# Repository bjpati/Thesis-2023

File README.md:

# Thesis-2023
The goal of this thesis is to develop an embedded test system for monitoring current in a multiple channel neuromuscular electrical stimulation (NMES) system. The system is designed to detect overcurrent and leakage conditions and protect the patient from injury.

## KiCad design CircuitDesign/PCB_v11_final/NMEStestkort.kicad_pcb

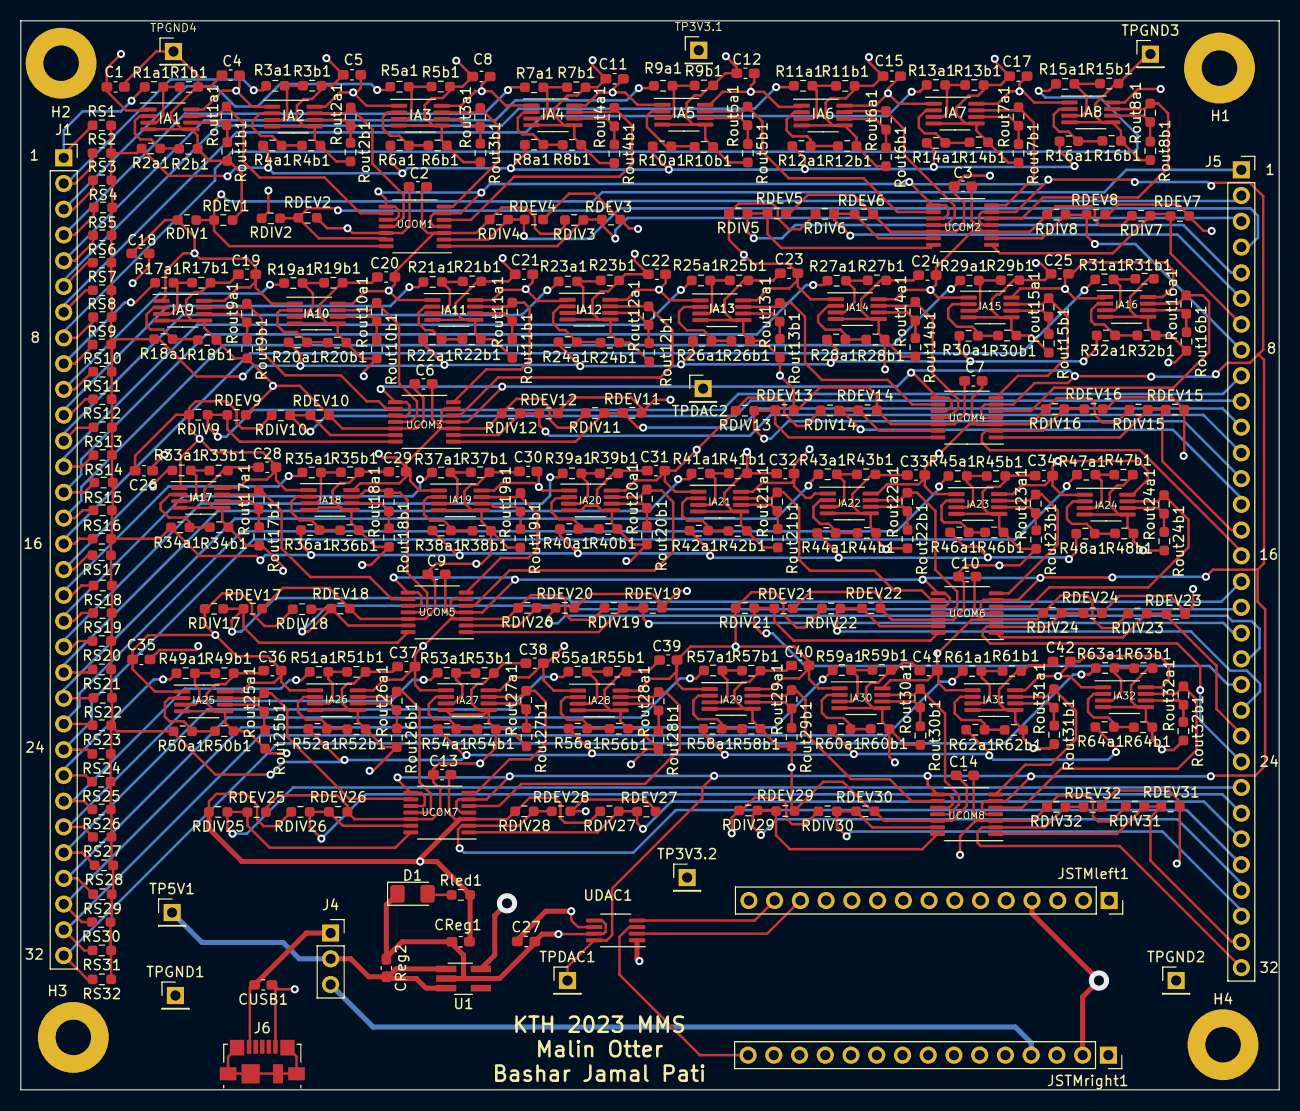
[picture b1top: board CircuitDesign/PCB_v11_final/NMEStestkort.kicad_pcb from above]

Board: 4 copper layers, 124.2 x 105.5 mm, 395 parts (0 on the bottom side), 203 nets.

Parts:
C1, C2, C3, C4, C5, C6, C7, C8, C9, C10, C11, C12, C13, C14, C15, C17, C18, C19, C20, C21, C22, C23, C24, C25, C26, C27, C28, C29, C30, C31, C32, C33, C34, C35, C36, C37, C38, C39, C40, C41, C42: 0.1u; C_0603_1608Metric_Pad1.08x0.95mm_HandSolder
CReg1, CReg2: 1u; C_0603_1608Metric_Pad1.08x0.95mm_HandSolder
CUSB1: 1u; C_0603_1608Metric_Pad1.08x0.95mm_HandSolder
D1: LED; LED_1206_3216Metric_Pad1.42x1.75mm_HandSolder
H1, H2, H3, H4: MountingHole; MountingHole_3.5mm_Pad
IA1, IA2, IA3, IA4, IA5, IA6, IA7, IA8, IA9, IA10, IA11, IA12, IA13, IA14, IA15, IA16, IA17, IA18, IA19, IA20, IA21, IA22, IA23, IA24, IA25, IA26, IA27, IA28, IA29, IA30, IA31, IA32: MCP6N16; MSOP-8_3x3mm_P0.65mm
J1, J5: Conn_01x32_Female; PinSocket_1x32_P2.54mm_Vertical
J4: Conn_01x03_Female; PinSocket_1x03_P2.54mm_Vertical
J6: USB_B_Micro; USB_Micro-B_Molex_47346-0001
JSTMleft1: Conn_01x15_Female; PinSocket_1x15_P2.54mm_Vertical
JSTMright1: Conn_01x15_Female; PinSocket_1x15_P2.54mm_Vertical
R1a1, R2a1, R3a1, R4a1, R5a1, R6a1, R7a1, R8a1, R9a1, R10a1, R11a1, R12a1, R13a1, R14a1, R15a1, R16a1, R17a1, R18a1, R19a1, R20a1, R21a1, R22a1, R23a1, R24a1, R25a1, R26a1, R27a1, R28a1, R29a1, R30a1, R31a1, R32a1, R33a1, R34a1, R35a1, R36a1, R37a1, R38a1, R39a1, R40a1, R41a1, R42a1, R43a1, R44a1, R45a1, R46a1, R47a1, R48a1, R49a1, R50a1, R51a1, R52a1, R53a1, R54a1, R55a1, R56a1, R57a1, R58a1, R59a1, R60a1, R61a1, R62a1, R63a1, R64a1: 47k; R_0603_1608Metric_Pad0.98x0.95mm_HandSolder
R1b1, R2b1, R3b1, R4b1, R5b1, R6b1, R7b1, R8b1, R9b1, R10b1, R11b1, R12b1, R13b1, R14b1, R15b1, R16b1, R17b1, R18b1, R19b1, R20b1, R21b1, R22b1, R23b1, R24b1, R25b1, R26b1, R27b1, R28b1, R29b1, R30b1, R31b1, R32b1, R33b1, R34b1, R35b1, R36b1, R37b1, R38b1, R39b1, R40b1, R41b1, R42b1, R43b1, R44b1, R45b1, R46b1, R47b1, R48b1, R49b1, R50b1, R51b1, R52b1, R53b1, R54b1, R55b1, R56b1, R57b1, R58b1, R59b1, R60b1, R61b1, R62b1, R63b1, R64b1: 470; R_0603_1608Metric_Pad0.98x0.95mm_HandSolder
RDEV1, RDEV2, RDEV3, RDEV4, RDEV5, RDEV6, RDEV7, RDEV8, RDEV9, RDEV10, RDEV11, RDEV12, RDEV13, RDEV14, RDEV15, RDEV16, RDEV17, RDEV18, RDEV19, RDEV20, RDEV21, RDEV22, RDEV23, RDEV24, RDEV25, RDEV26, RDEV27, RDEV28, RDEV29, RDEV30, RDEV31, RDEV32: 6k2; R_0603_1608Metric_Pad0.98x0.95mm_HandSolder
RDIV1, RDIV2, RDIV3, RDIV4, RDIV5, RDIV6, RDIV7, RDIV8, RDIV9, RDIV10, RDIV11, RDIV12, RDIV13, RDIV14, RDIV15, RDIV16, RDIV17, RDIV18, RDIV19, RDIV20, RDIV21, RDIV22, RDIV23, RDIV24, RDIV25, RDIV26, RDIV27, RDIV28, RDIV29, RDIV30, RDIV31, RDIV32: 2k2; R_0603_1608Metric_Pad0.98x0.95mm_HandSolder
RS1, RS2, RS3, RS4, RS5, RS6, RS7, RS8, RS9, RS10, RS11, RS12, RS13, RS14, RS15, RS16, RS17, RS18, RS19, RS20, RS21, RS22, RS23, RS24, RS25, RS26, RS27, RS28, RS29, RS30, RS31, RS32: 500; R_0603_1608Metric_Pad0.98x0.95mm_HandSolder
Rled1: 1k; R_0603_1608Metric_Pad0.98x0.95mm_HandSolder
Rout1a1, Rout2a1, Rout3a1, Rout4a1, Rout5a1, Rout6a1, Rout7a1, Rout8a1, Rout9a1, Rout10a1, Rout11a1, Rout12a1, Rout13a1, Rout14a1, Rout15a1, Rout16a1, Rout17a1, Rout18a1, Rout19a1, Rout20a1, Rout21a1, Rout22a1, Rout23a1, Rout24a1, Rout25a1, Rout26a1, Rout27a1, Rout28a1, Rout29a1, Rout30a1, Rout31a1, Rout32a1: 12k; R_0603_1608Metric_Pad0.98x0.95mm_HandSolder
Rout1b1, Rout2b1, Rout3b1, Rout4b1, Rout5b1, Rout6b1, Rout7b1, Rout8b1, Rout9b1, Rout10b1, Rout11b1, Rout12b1, Rout13b1, Rout14b1, Rout15b1, Rout16b1, Rout17b1, Rout18b1, Rout19b1, Rout20b1, Rout21b1, Rout22b1, Rout23b1, Rout24b1, Rout25b1, Rout26b1, Rout27b1, Rout28b1, Rout29b1, Rout30b1, Rout31b1, Rout32b1: 1k; R_0603_1608Metric_Pad0.98x0.95mm_HandSolder
TP3V3.1, TP3V3.2: Conn_01x02_Female; PinHeader_1x01_P2.54mm_Vertical
TP5V1: Conn_01x01_Female; PinHeader_1x01_P2.54mm_Vertical
TPDAC1, TPDAC2: Conn_01x01_Female; PinHeader_1x01_P2.54mm_Vertical
TPGND1, TPGND2, TPGND3, TPGND4: Conn_01x02_Female; PinHeader_1x01_P2.54mm_Vertical
U1: ADP151; TSOT-23-5_HandSoldering
UCOM1, UCOM2, UCOM3, UCOM4, UCOM5, UCOM6, UCOM7, UCOM8: LM339; TSSOP-14_4.4x5mm_P0.65mm
UDAC1: MCP4921; MSOP-8_3x3mm_P0.65mm

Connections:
+3.3V: C1.1, C2.1, C3.1, C4.1, C5.1, C6.1, C7.1, C8.1, C9.1, C10.1, C11.1, C12.1, C13.1, C14.1, C15.1, C17.1, C18.1, C19.1, C20.1, C21.1, C22.1, C23.1, C24.1, C25.1, C26.1, C27.1, C28.1, C29.1, C30.1, C31.1, C32.1, C33.1, C34.1, C35.1, C36.1, C37.1, C38.1, C39.1, C40.1, C41.1, C42.1, CReg1.1, IA1.1 (EN), IA1.8 (V+), IA2.1 (EN), IA2.8 (V+), IA3.1 (EN), IA3.8 (V+), IA4.1 (EN), IA4.8 (V+), IA5.1 (EN), IA5.8 (V+), IA6.1 (EN), IA6.8 (V+), IA7.1 (EN), IA7.8 (V+), IA8.1 (EN), IA8.8 (V+), IA9.1 (EN), IA9.8 (V+), IA10.1 (EN), IA10.8 (V+), IA11.1 (EN), IA11.8 (V+), IA12.1 (EN), IA12.8 (V+), IA13.1 (EN), IA13.8 (V+), IA14.1 (EN), IA14.8 (V+), IA15.1 (EN), IA15.8 (V+), IA16.1 (EN), IA16.8 (V+), IA17.1 (EN), IA17.8 (V+), IA18.1 (EN), IA18.8 (V+), IA19.1 (EN), IA19.8 (V+), IA20.1 (EN), IA20.8 (V+), IA21.1 (EN), IA21.8 (V+), IA22.1 (EN), IA22.8 (V+), IA23.1 (EN), IA23.8 (V+), IA24.1 (EN), IA24.8 (V+), IA25.1 (EN), IA25.8 (V+), IA26.1 (EN), IA26.8 (V+), IA27.1 (EN), IA27.8 (V+), IA28.1 (EN), IA28.8 (V+), IA29.1 (EN), IA29.8 (V+), IA30.1 (EN), IA30.8 (V+), IA31.1 (EN), IA31.8 (V+), IA32.1 (EN), IA32.8 (V+), RDIV1.2, RDIV2.2, RDIV3.2, RDIV4.2, RDIV5.2, RDIV6.2, RDIV7.2, RDIV8.2, RDIV9.2, RDIV10.2, RDIV11.2, RDIV12.2, RDIV13.2, RDIV14.2, RDIV15.2, RDIV16.2, RDIV17.2, RDIV18.2, RDIV19.2, RDIV20.2, RDIV21.2, RDIV22.2, RDIV23.2, RDIV24.2, RDIV25.2, RDIV26.2, RDIV27.2, RDIV28.2, RDIV29.2, RDIV30.2, RDIV31.2, RDIV32.2, Rled1.2, TP3V3.1.1, TP3V3.2.1, U1.5 (VOUT), UCOM1.3 (V+), UCOM2.3 (V+), UCOM3.3 (V+), UCOM4.3 (V+), UCOM5.3 (V+), UCOM6.3 (V+), UCOM7.3 (V+), UCOM8.3 (V+), UDAC1.1 (Vdd), UDAC1.6 (Vref)
+5V: CReg2.2, J4.2, TP5V1.1, U1.1 (VIN), U1.3 (EN)
+5V MCU: J4.3, JSTMright1.4
+5V USB: CUSB1.2, J4.1, J6.1 (VBUS)
DAC output: TPDAC1.1, TPDAC2.1, UCOM1.4 (-), UCOM1.6 (-), UCOM1.8 (-), UCOM1.10 (-), UCOM2.4 (-), UCOM2.6 (-), UCOM2.8 (-), UCOM2.10 (-), UCOM3.4 (-), UCOM3.6 (-), UCOM3.8 (-), UCOM3.10 (-), UCOM4.4 (-), UCOM4.6 (-), UCOM4.8 (-), UCOM4.10 (-), UCOM5.4 (-), UCOM5.6 (-), UCOM5.8 (-), UCOM5.10 (-), UCOM6.4 (-), UCOM6.6 (-), UCOM6.8 (-), UCOM6.10 (-), UCOM7.4 (-), UCOM7.6 (-), UCOM7.8 (-), UCOM7.10 (-), UCOM8.4 (-), UCOM8.6 (-), UCOM8.8 (-), UCOM8.10 (-), UDAC1.8 (Vout)
GND: C1.2, C2.2, C3.2, C4.2, C5.2, C6.2, C7.2, C8.2, C9.2, C10.2, C11.2, C12.2, C13.2, C14.2, C15.2, C17.2, C18.2, C19.2, C20.2, C21.2, C22.2, C23.2, C24.2, C25.2, C26.2, C27.2, C28.2, C29.2, C30.2, C31.2, C32.2, C33.2, C34.2, C35.2, C36.2, C37.2, C38.2, C39.2, C40.2, C41.2, C42.2, CReg1.2, CReg2.1, CUSB1.1, D1.1 (K), IA1.4 (V-), IA1.5 (Vref), IA2.4 (V-), IA2.5 (Vref), IA3.4 (V-), IA3.5 (Vref), IA4.4 (V-), IA4.5 (Vref), IA5.4 (V-), IA5.5 (Vref), IA6.4 (V-), IA6.5 (Vref), IA7.4 (V-), IA7.5 (Vref), IA8.4 (V-), IA8.5 (Vref), IA9.4 (V-), IA9.5 (Vref), IA10.4 (V-), IA10.5 (Vref), IA11.4 (V-), IA11.5 (Vref), IA12.4 (V-), IA12.5 (Vref), IA13.4 (V-), IA13.5 (Vref), IA14.4 (V-), IA14.5 (Vref), IA15.4 (V-), IA15.5 (Vref), IA16.4 (V-), IA16.5 (Vref), IA17.4 (V-), IA17.5 (Vref), IA18.4 (V-), IA18.5 (Vref), IA19.4 (V-), IA19.5 (Vref), IA20.4 (V-), IA20.5 (Vref), IA21.4 (V-), IA21.5 (Vref), IA22.4 (V-), IA22.5 (Vref), IA23.4 (V-), IA23.5 (Vref), IA24.4 (V-), IA24.5 (Vref), IA25.4 (V-), IA25.5 (Vref), IA26.4 (V-), IA26.5 (Vref), IA27.4 (V-), IA27.5 (Vref), IA28.4 (V-), IA28.5 (Vref), IA29.4 (V-), IA29.5 (Vref), IA30.4 (V-), IA30.5 (Vref), IA31.4 (V-), IA31.5 (Vref), IA32.4 (V-), IA32.5 (Vref), J6.5 (GND), JSTMleft1.4, JSTMright1.2, R1b1.2, R2b1.2, R3b1.2, R4b1.2, R5b1.2, R6b1.2, R7b1.2, R8b1.2, R9b1.2, R10b1.2, R11b1.2, R12b1.2, R13b1.2, R14b1.2, R15b1.2, R16b1.2, R17b1.2, R18b1.2, R19b1.2, R20b1.2, R21b1.2, R22b1.2, R23b1.2, R24b1.2, R25b1.2, R26b1.2, R27b1.2, R28b1.2, R29b1.2, R30b1.2, R31b1.2, R32b1.2, R33b1.2, R34b1.2, R35b1.2, R36b1.2, R37b1.2, R38b1.2, R39b1.2, R40b1.2, R41b1.2, R42b1.2, R43b1.2, R44b1.2, R45b1.2, R46b1.2, R47b1.2, R48b1.2, R49b1.2, R50b1.2, R51b1.2, R52b1.2, R53b1.2, R54b1.2, R55b1.2, R56b1.2, R57b1.2, R58b1.2, R59b1.2, R60b1.2, R61b1.2, R62b1.2, R63b1.2, R64b1.2, RDEV1.1, RDEV2.1, RDEV3.1, RDEV4.1, RDEV5.1, RDEV6.1, RDEV7.1, RDEV8.1, RDEV9.1, RDEV10.1, RDEV11.1, RDEV12.1, RDEV13.1, RDEV14.1, RDEV15.1, RDEV16.1, RDEV17.1, RDEV18.1, RDEV19.1, RDEV20.1, RDEV21.1, RDEV22.1, RDEV23.1, RDEV24.1, RDEV25.1, RDEV26.1, RDEV27.1, RDEV28.1, RDEV29.1, RDEV30.1, RDEV31.1, RDEV32.1, Rout1b1.2, Rout2b1.2, Rout3b1.2, Rout4b1.2, Rout5b1.2, Rout6b1.2, Rout7b1.2, Rout8b1.2, Rout9b1.2, Rout10b1.2, Rout11b1.2, Rout12b1.2, Rout13b1.2, Rout14b1.2, Rout15b1.2, Rout16b1.2, Rout17b1.2, Rout18b1.2, Rout19b1.2, Rout20b1.2, Rout21b1.2, Rout22b1.2, Rout23b1.2, Rout24b1.2, Rout25b1.2, Rout26b1.2, Rout27b1.2, Rout28b1.2, Rout29b1.2, Rout30b1.2, Rout31b1.2, Rout32b1.2, TPGND1.1, TPGND2.1, TPGND3.1, TPGND4.1, U1.2 (GND), UCOM1.12 (V-), UCOM2.12 (V-), UCOM3.12 (V-), UCOM4.12 (V-), UCOM5.12 (V-), UCOM6.12 (V-), UCOM7.12 (V-), UCOM8.12 (V-), UDAC1.5 (~LDAC), UDAC1.7 (Vss)
unnamed: D1.2 (A), Rled1.1
unnamed: IA1.2 (-), R2a1.1, R2b1.1
unnamed: IA1.3 (+), R1a1.1, R1b1.1
unnamed: IA1.6 (Vfg), Rout1a1.1, Rout1b1.1
unnamed: IA1.7 (Vout), Rout1a1.2, UCOM1.9 (+)
unnamed: IA2.2 (-), R4a1.1, R4b1.1
unnamed: IA2.3 (+), R3a1.1, R3b1.1
unnamed: IA2.6 (Vfg), Rout2a1.1, Rout2b1.1
unnamed: IA2.7 (Vout), Rout2a1.2, UCOM1.11 (+)
unnamed: IA3.2 (-), R6a1.1, R6b1.1
unnamed: IA3.3 (+), R5a1.1, R5b1.1
unnamed: IA3.6 (Vfg), Rout3a1.1, Rout3b1.1
unnamed: IA3.7 (Vout), Rout3a1.2, UCOM1.7 (+)
unnamed: IA4.2 (-), R8a1.1, R8b1.1
unnamed: IA4.3 (+), R7a1.1, R7b1.1
unnamed: IA4.6 (Vfg), Rout4a1.1, Rout4b1.1
unnamed: IA4.7 (Vout), Rout4a1.2, UCOM1.5 (+)
unnamed: IA5.2 (-), R10a1.1, R10b1.1
unnamed: IA5.3 (+), R9a1.1, R9b1.1
unnamed: IA5.6 (Vfg), Rout5a1.1, Rout5b1.1
unnamed: IA5.7 (Vout), Rout5a1.2, UCOM2.9 (+)
unnamed: IA6.2 (-), R12a1.1, R12b1.1
unnamed: IA6.3 (+), R11a1.1, R11b1.1
unnamed: IA6.6 (Vfg), Rout6a1.1, Rout6b1.1
unnamed: IA6.7 (Vout), Rout6a1.2, UCOM2.11 (+)
unnamed: IA7.2 (-), R14a1.1, R14b1.1
unnamed: IA7.3 (+), R13a1.1, R13b1.1
unnamed: IA7.6 (Vfg), Rout7a1.1, Rout7b1.1
unnamed: IA7.7 (Vout), Rout7a1.2, UCOM2.7 (+)
unnamed: IA8.2 (-), R16a1.1, R16b1.1
unnamed: IA8.3 (+), R15a1.1, R15b1.1
unnamed: IA8.6 (Vfg), Rout8a1.1, Rout8b1.1
unnamed: IA8.7 (Vout), Rout8a1.2, UCOM2.5 (+)
unnamed: IA9.2 (-), R18a1.1, R18b1.1
unnamed: IA9.3 (+), R17a1.1, R17b1.1
unnamed: IA9.6 (Vfg), Rout9a1.1, Rout9b1.1
unnamed: IA9.7 (Vout), Rout9a1.2, UCOM3.9 (+)
unnamed: IA10.2 (-), R20a1.1, R20b1.1
unnamed: IA10.3 (+), R19a1.1, R19b1.1
unnamed: IA10.6 (Vfg), Rout10a1.1, Rout10b1.1
unnamed: IA10.7 (Vout), Rout10a1.2, UCOM3.11 (+)
unnamed: IA11.2 (-), R22a1.1, R22b1.1
unnamed: IA11.3 (+), R21a1.1, R21b1.1
unnamed: IA11.6 (Vfg), Rout11a1.1, Rout11b1.1
unnamed: IA11.7 (Vout), Rout11a1.2, UCOM3.7 (+)
unnamed: IA12.2 (-), R24a1.1, R24b1.1
unnamed: IA12.3 (+), R23a1.1, R23b1.1
unnamed: IA12.6 (Vfg), Rout12a1.1, Rout12b1.1
unnamed: IA12.7 (Vout), Rout12a1.2, UCOM3.5 (+)
unnamed: IA13.2 (-), R26a1.1, R26b1.1
unnamed: IA13.3 (+), R25a1.1, R25b1.1
unnamed: IA13.6 (Vfg), Rout13a1.1, Rout13b1.1
unnamed: IA13.7 (Vout), Rout13a1.2, UCOM4.9 (+)
unnamed: IA14.2 (-), R28a1.1, R28b1.1
unnamed: IA14.3 (+), R27a1.1, R27b1.1
unnamed: IA14.6 (Vfg), Rout14a1.1, Rout14b1.1
unnamed: IA14.7 (Vout), Rout14a1.2, UCOM4.11 (+)
unnamed: IA15.2 (-), R30a1.1, R30b1.1
unnamed: IA15.3 (+), R29a1.1, R29b1.1
unnamed: IA15.6 (Vfg), Rout15a1.1, Rout15b1.1
unnamed: IA15.7 (Vout), Rout15a1.2, UCOM4.7 (+)
unnamed: IA16.2 (-), R32a1.1, R32b1.1
unnamed: IA16.3 (+), R31a1.1, R31b1.1
unnamed: IA16.6 (Vfg), Rout16a1.1, Rout16b1.1
unnamed: IA16.7 (Vout), Rout16a1.2, UCOM4.5 (+)
unnamed: IA17.2 (-), R34a1.1, R34b1.1
unnamed: IA17.3 (+), R33a1.1, R33b1.1
unnamed: IA17.6 (Vfg), Rout17a1.1, Rout17b1.1
unnamed: IA17.7 (Vout), Rout17a1.2, UCOM5.9 (+)
unnamed: IA18.2 (-), R36a1.1, R36b1.1
unnamed: IA18.3 (+), R35a1.1, R35b1.1
unnamed: IA18.6 (Vfg), Rout18a1.1, Rout18b1.1
unnamed: IA18.7 (Vout), Rout18a1.2, UCOM5.11 (+)
unnamed: IA19.2 (-), R38a1.1, R38b1.1
unnamed: IA19.3 (+), R37a1.1, R37b1.1
unnamed: IA19.6 (Vfg), Rout19a1.1, Rout19b1.1
unnamed: IA19.7 (Vout), Rout19a1.2, UCOM5.7 (+)
unnamed: IA20.2 (-), R40a1.1, R40b1.1
unnamed: IA20.3 (+), R39a1.1, R39b1.1
unnamed: IA20.6 (Vfg), Rout20a1.1, Rout20b1.1
unnamed: IA20.7 (Vout), Rout20a1.2, UCOM5.5 (+)
unnamed: IA21.2 (-), R42a1.1, R42b1.1
unnamed: IA21.3 (+), R41a1.1, R41b1.1
unnamed: IA21.6 (Vfg), Rout21a1.1, Rout21b1.1
unnamed: IA21.7 (Vout), Rout21a1.2, UCOM6.9 (+)
unnamed: IA22.2 (-), R44a1.1, R44b1.1
unnamed: IA22.3 (+), R43a1.1, R43b1.1
unnamed: IA22.6 (Vfg), Rout22a1.1, Rout22b1.1
unnamed: IA22.7 (Vout), Rout22a1.2, UCOM6.11 (+)
unnamed: IA23.2 (-), R46a1.1, R46b1.1
unnamed: IA23.3 (+), R45a1.1, R45b1.1
unnamed: IA23.6 (Vfg), Rout23a1.1, Rout23b1.1
unnamed: IA23.7 (Vout), Rout23a1.2, UCOM6.7 (+)
unnamed: IA24.2 (-), R48a1.1, R48b1.1
unnamed: IA24.3 (+), R47a1.1, R47b1.1
unnamed: IA24.6 (Vfg), Rout24a1.1, Rout24b1.1
unnamed: IA24.7 (Vout), Rout24a1.2, UCOM6.5 (+)
unnamed: IA25.2 (-), R50a1.1, R50b1.1
unnamed: IA25.3 (+), R49a1.1, R49b1.1
unnamed: IA25.6 (Vfg), Rout25a1.1, Rout25b1.1
unnamed: IA25.7 (Vout), Rout25a1.2, UCOM7.9 (+)
unnamed: IA26.2 (-), R52a1.1, R52b1.1
unnamed: IA26.3 (+), R51a1.1, R51b1.1
unnamed: IA26.6 (Vfg), Rout26a1.1, Rout26b1.1
unnamed: IA26.7 (Vout), Rout26a1.2, UCOM7.11 (+)
unnamed: IA27.2 (-), R54a1.1, R54b1.1
unnamed: IA27.3 (+), R53a1.1, R53b1.1
unnamed: IA27.6 (Vfg), Rout27a1.1, Rout27b1.1
unnamed: IA27.7 (Vout), Rout27a1.2, UCOM7.7 (+)
unnamed: IA28.2 (-), R56a1.1, R56b1.1
unnamed: IA28.3 (+), R55a1.1, R55b1.1
unnamed: IA28.6 (Vfg), Rout28a1.1, Rout28b1.1
unnamed: IA28.7 (Vout), Rout28a1.2, UCOM7.5 (+)
unnamed: IA29.2 (-), R58a1.1, R58b1.1
unnamed: IA29.3 (+), R57a1.1, R57b1.1
unnamed: IA29.6 (Vfg), Rout29a1.1, Rout29b1.1
unnamed: IA29.7 (Vout), Rout29a1.2, UCOM8.9 (+)
unnamed: IA30.2 (-), R60a1.1, R60b1.1
unnamed: IA30.3 (+), R59a1.1, R59b1.1
unnamed: IA30.6 (Vfg), Rout30a1.1, Rout30b1.1
unnamed: IA30.7 (Vout), Rout30a1.2, UCOM8.11 (+)
unnamed: IA31.2 (-), R62a1.1, R62b1.1
unnamed: IA31.3 (+), R61a1.1, R61b1.1
unnamed: IA31.6 (Vfg), Rout31a1.1, Rout31b1.1
unnamed: IA31.7 (Vout), Rout31a1.2, UCOM8.7 (+)
unnamed: IA32.2 (-), R64a1.1, R64b1.1
unnamed: IA32.3 (+), R63a1.1, R63b1.1
unnamed: IA32.6 (Vfg), Rout32a1.1, Rout32b1.1
unnamed: IA32.7 (Vout), Rout32a1.2, UCOM8.5 (+)
unnamed: J1.1, R1a1.2, RS1.2
unnamed: J1.2, R3a1.2, RS2.2
unnamed: J1.3, R5a1.2, RS3.2
unnamed: J1.4, R7a1.2, RS4.2
unnamed: J1.5, R9a1.2, RS5.2
unnamed: J1.6, R11a1.2, RS6.2
unnamed: J1.7, R13a1.2, RS7.2
unnamed: J1.8, R15a1.2, RS8.2
unnamed: J1.9, R17a1.2, RS9.2
unnamed: J1.10, R19a1.2, RS10.2
unnamed: J1.11, R21a1.2, RS11.2
unnamed: J1.12, R23a1.2, RS12.2
unnamed: J1.13, R25a1.2, RS13.2
unnamed: J1.14, R27a1.2, RS14.2
unnamed: J1.15, R29a1.2, RS15.2
unnamed: J1.16, R31a1.2, RS16.2
unnamed: J1.17, R33a1.2, RS17.2
unnamed: J1.18, R35a1.2, RS18.2
unnamed: J1.19, R37a1.2, RS19.2
unnamed: J1.20, R39a1.2, RS20.2
unnamed: J1.21, R41a1.2, RS21.2
unnamed: J1.22, R43a1.2, RS22.2
unnamed: J1.23, R45a1.2, RS23.2
unnamed: J1.24, R47a1.2, RS24.2
unnamed: J1.25, R49a1.2, RS25.2
unnamed: J1.26, R51a1.2, RS26.2
unnamed: J1.27, R53a1.2, RS27.2
unnamed: J1.28, R55a1.2, RS28.2
unnamed: J1.29, R57a1.2, RS29.2
unnamed: J1.30, R59a1.2, RS30.2
unnamed: J1.31, R61a1.2, RS31.2
unnamed: J1.32, R63a1.2, RS32.2
unnamed: J5.1, RDEV1.2, RDIV1.1, UCOM1.14
unnamed: J5.2, RDEV2.2, RDIV2.1, UCOM1.13
unnamed: J5.3, RDEV3.2, RDIV3.1, UCOM1.1
unnamed: J5.4, RDEV4.2, RDIV4.1, UCOM1.2
unnamed: J5.5, RDEV5.2, RDIV5.1, UCOM2.14
unnamed: J5.6, RDEV6.2, RDIV6.1, UCOM2.13
unnamed: J5.7, RDEV7.2, RDIV7.1, UCOM2.1
unnamed: J5.8, RDEV8.2, RDIV8.1, UCOM2.2
unnamed: J5.9, RDEV9.2, RDIV9.1, UCOM3.14
unnamed: J5.10, RDEV10.2, RDIV10.1, UCOM3.13
unnamed: J5.11, RDEV11.2, RDIV11.1, UCOM3.1
unnamed: J5.12, RDEV12.2, RDIV12.1, UCOM3.2
unnamed: J5.13, RDEV13.2, RDIV13.1, UCOM4.14
unnamed: J5.14, RDEV14.2, RDIV14.1, UCOM4.13
unnamed: J5.15, RDEV15.2, RDIV15.1, UCOM4.1
unnamed: J5.16, RDEV16.2, RDIV16.1, UCOM4.2
unnamed: J5.17, RDEV17.2, RDIV17.1, UCOM5.14
unnamed: J5.18, RDEV18.2, RDIV18.1, UCOM5.13
unnamed: J5.19, RDEV19.2, RDIV19.1, UCOM5.1
unnamed: J5.20, RDEV20.2, RDIV20.1, UCOM5.2
unnamed: J5.21, RDEV21.2, RDIV21.1, UCOM6.14
unnamed: J5.22, RDEV22.2, RDIV22.1, UCOM6.13
unnamed: J5.23, RDEV23.2, RDIV23.1, UCOM6.1
unnamed: J5.24, RDEV24.2, RDIV24.1, UCOM6.2
unnamed: J5.25, RDEV25.2, RDIV25.1, UCOM7.14
unnamed: J5.26, RDEV26.2, RDIV26.1, UCOM7.13
unnamed: J5.27, RDEV27.2, RDIV27.1, UCOM7.1
unnamed: J5.28, RDEV28.2, RDIV28.1, UCOM7.2
unnamed: J5.29, RDEV29.2, RDIV29.1, UCOM8.14
unnamed: J5.30, RDEV30.2, RDIV30.1, UCOM8.13
unnamed: J5.31, RDEV31.2, RDIV31.1, UCOM8.1
unnamed: J5.32, RDEV32.2, RDIV32.1, UCOM8.2
unnamed: R2a1.2, R4a1.2, R6a1.2, R8a1.2, R10a1.2, R12a1.2, R14a1.2, R16a1.2, R18a1.2, R20a1.2, R22a1.2, R24a1.2, R26a1.2, R28a1.2, R30a1.2, R32a1.2, R34a1.2, R36a1.2, R38a1.2, R40a1.2, R42a1.2, R44a1.2, R46a1.2, R48a1.2, R50a1.2, R52a1.2, R54a1.2, R56a1.2, R58a1.2, R60a1.2, R62a1.2, R64a1.2, RS1.1, RS2.1, RS3.1, RS4.1, RS5.1, RS6.1, RS7.1, RS8.1, RS9.1, RS10.1, RS11.1, RS12.1, RS13.1, RS14.1, RS15.1, RS16.1, RS17.1, RS18.1, RS19.1, RS20.1, RS21.1, RS22.1, RS23.1, RS24.1, RS25.1, RS26.1, RS27.1, RS28.1, RS29.1, RS30.1, RS31.1, RS32.1
SCK: JSTMright1.15, UDAC1.3 (SCK)
SPI_CS: JSTMleft1.13, UDAC1.2 (~CS)
SPI_MOSI: JSTMleft1.14, UDAC1.4 (SDI)
